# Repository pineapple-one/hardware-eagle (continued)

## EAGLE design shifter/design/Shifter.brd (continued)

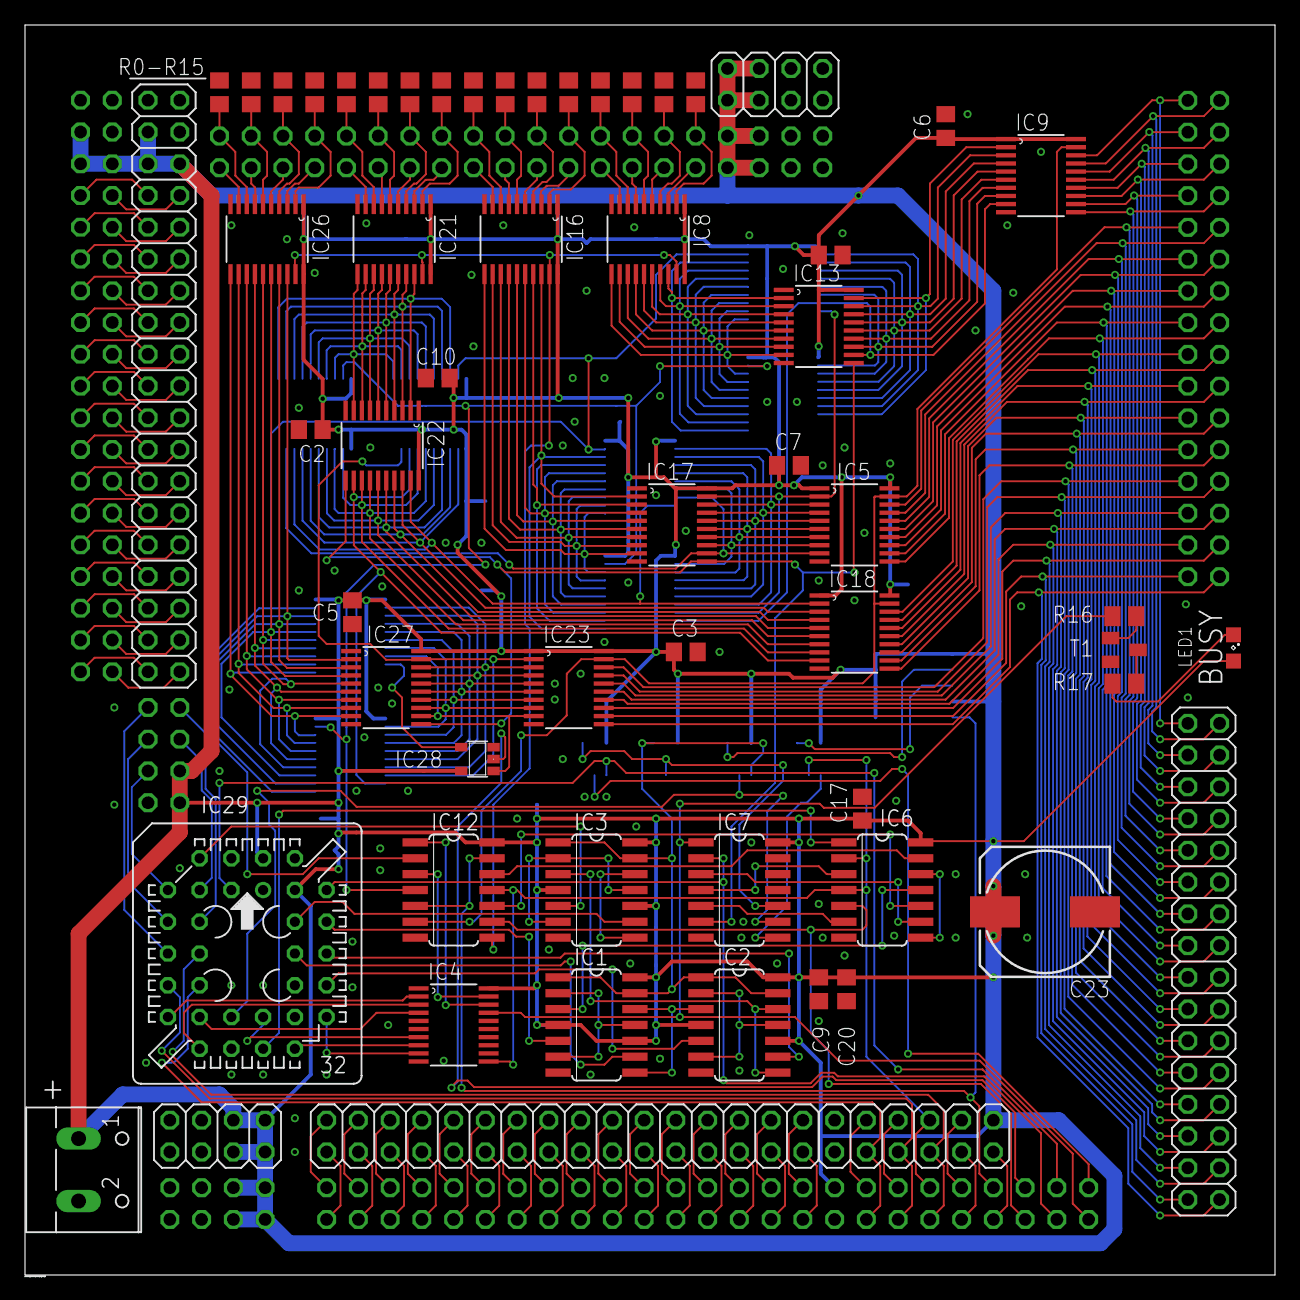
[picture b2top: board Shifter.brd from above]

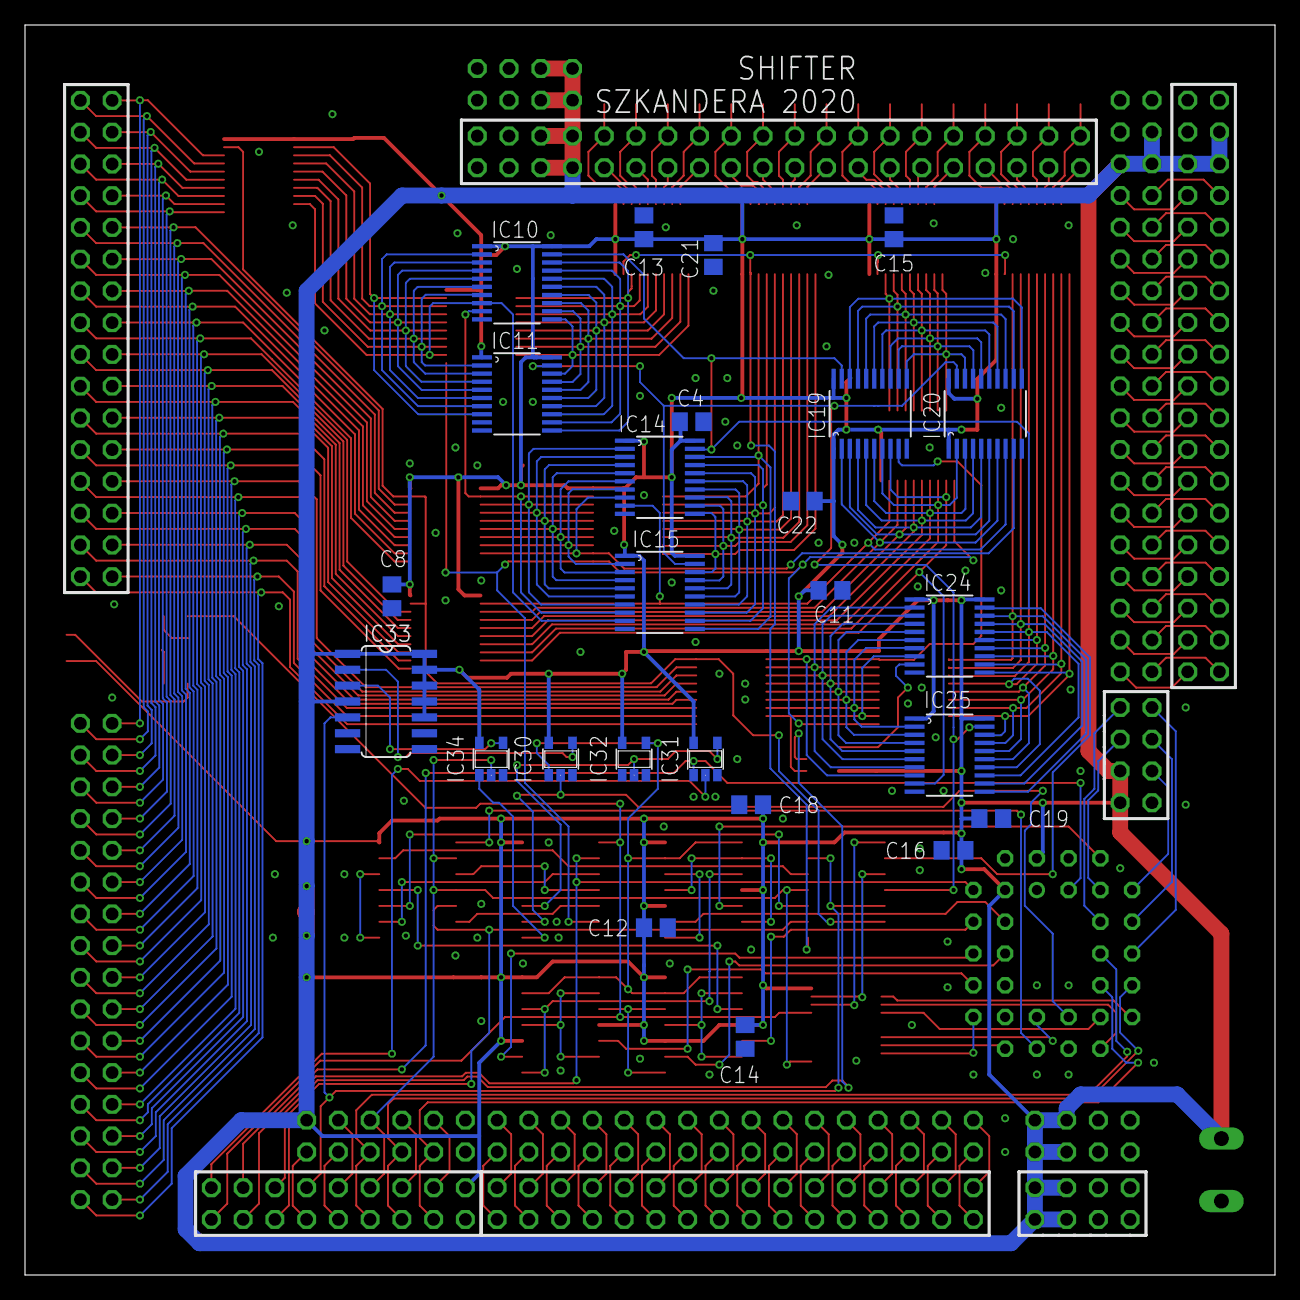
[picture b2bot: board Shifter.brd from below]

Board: 2 copper layers, 100.0 x 100.0 mm, 91 parts (25 on the bottom side), 258 nets.

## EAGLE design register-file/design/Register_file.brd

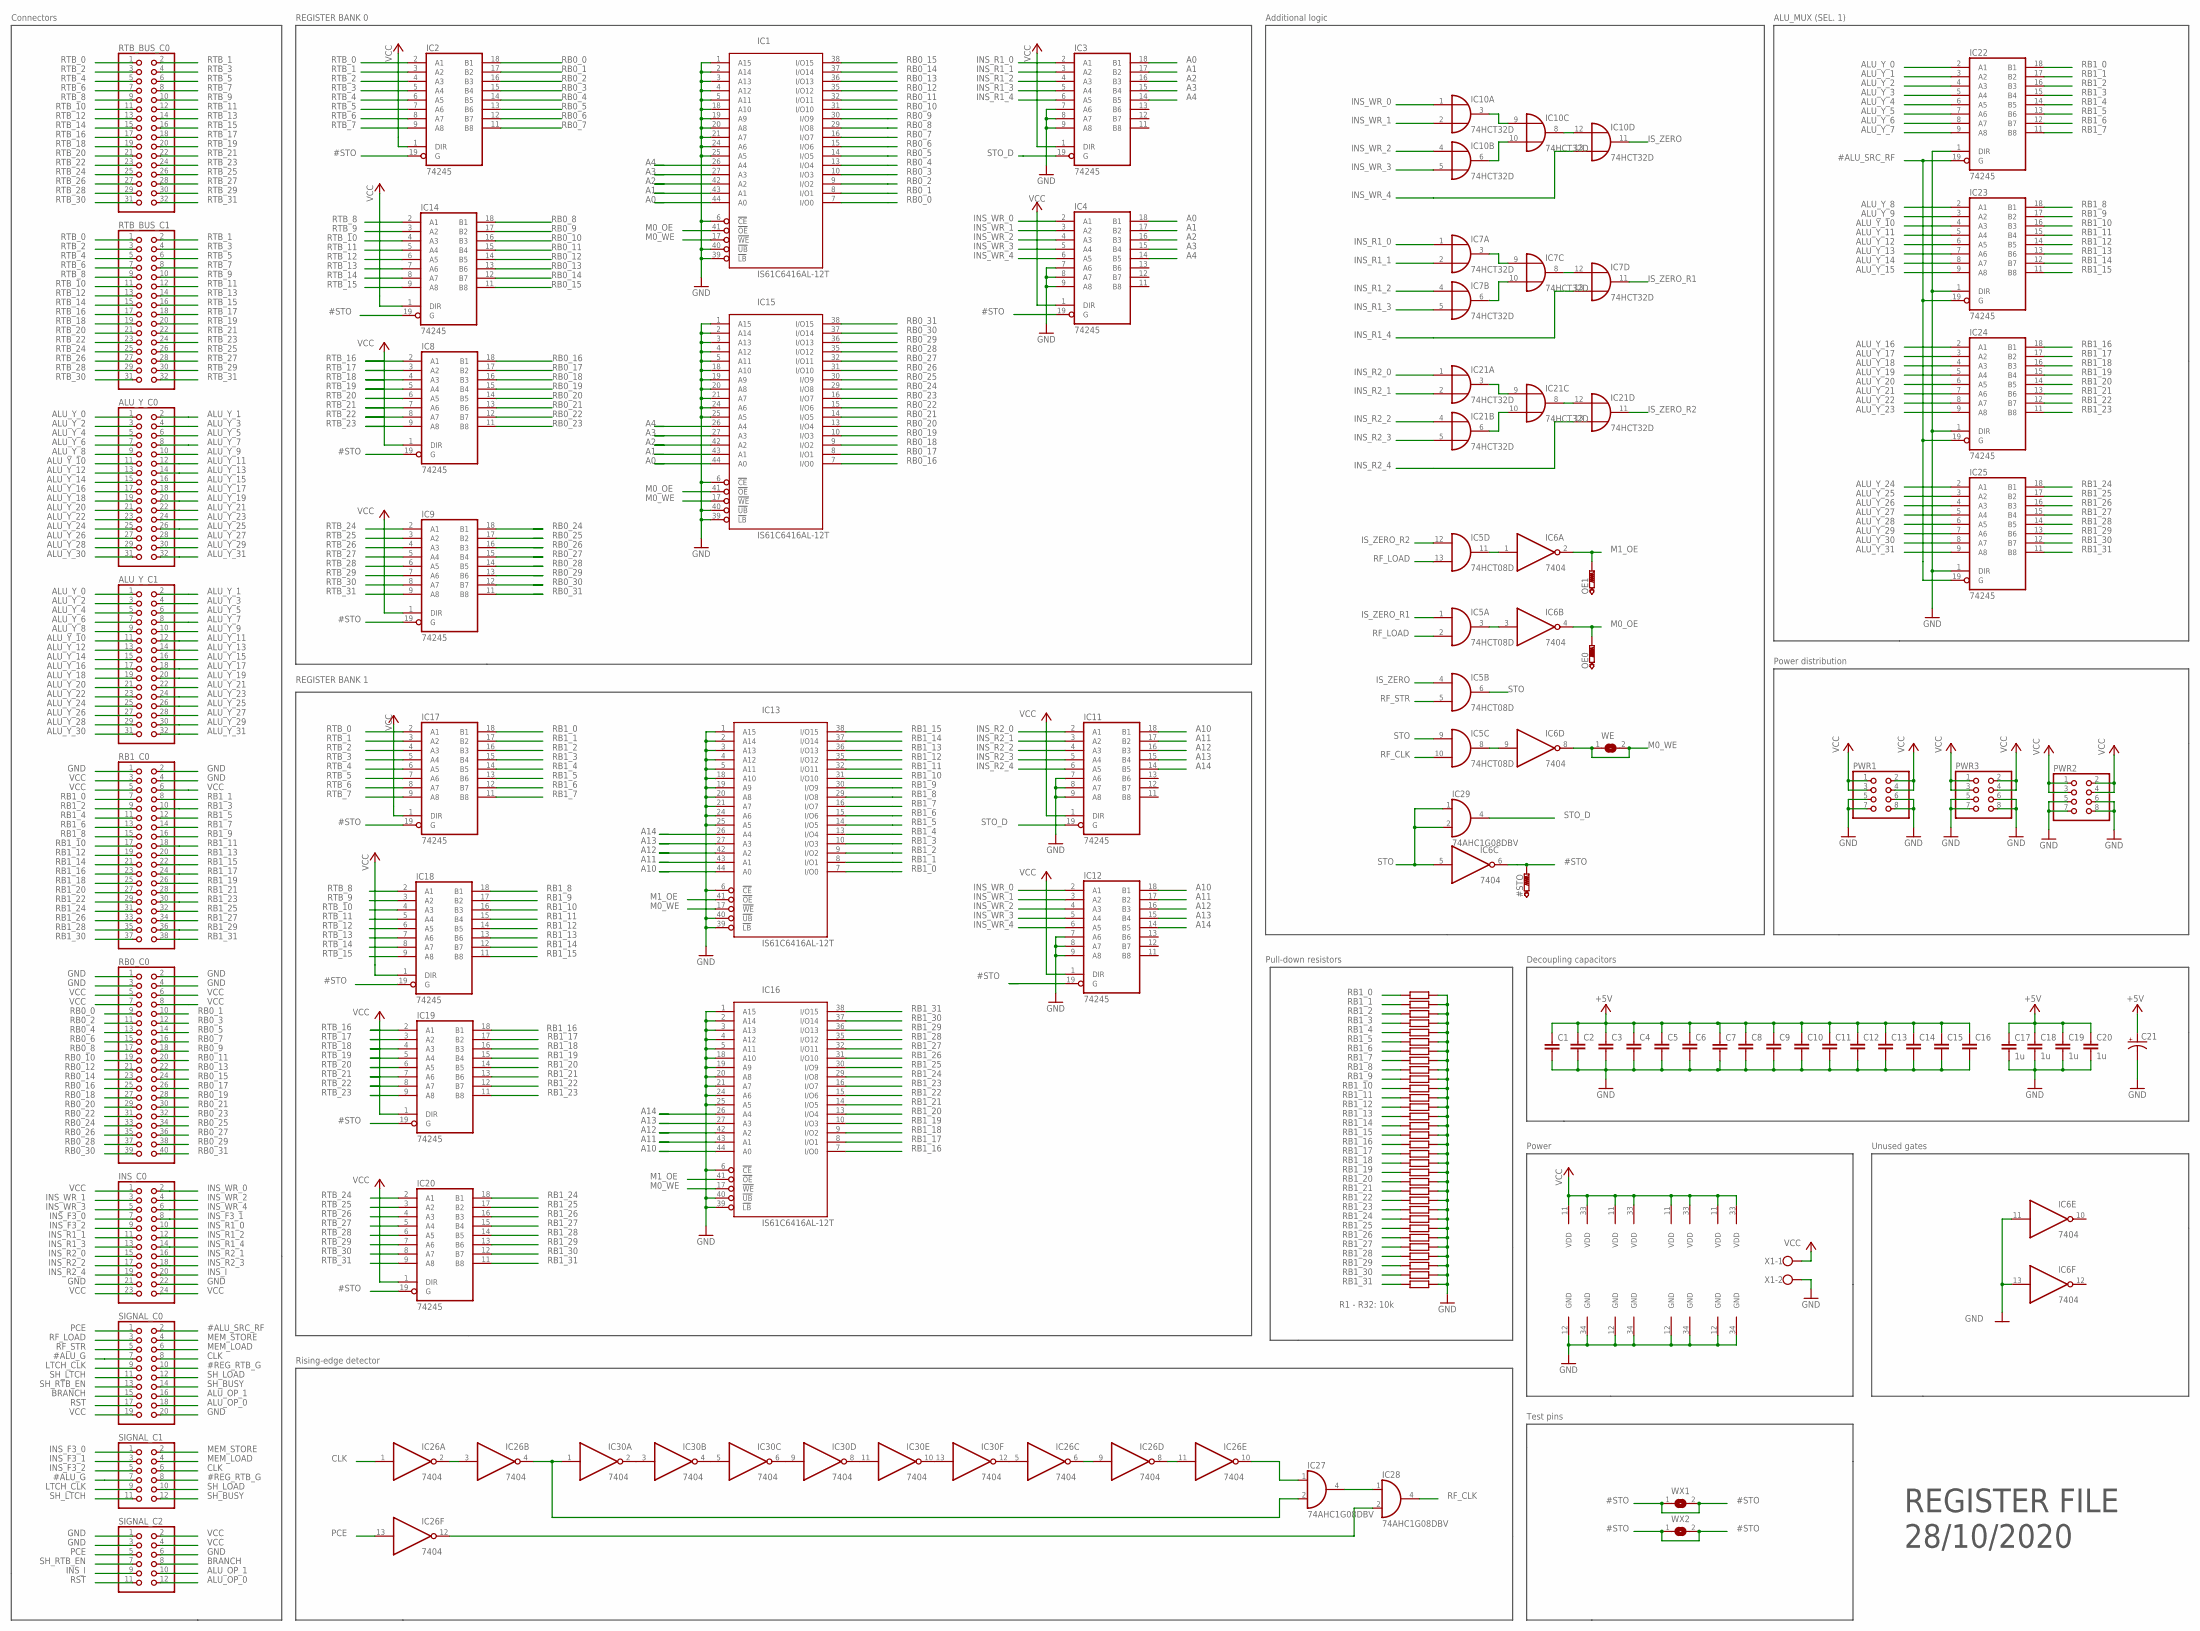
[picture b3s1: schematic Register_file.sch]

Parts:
#STO: PTR1B2,54; B2,54
ALU_Y_C0, ALU_Y_C1: PINHD-2X16; 2X16
C1, C2, C3, C4, C5, C6, C7, C8, C9, C10, C11, C12, C13, C14, C15, C16: C-EUC0805; C0805
C17, C18, C19, C20: 1u; C0805
C21: CAPACITOR-P153CLV-1010; 153CLV-1010
IC1, IC13, IC15, IC16: IS61C6416AL-12T; TSOP-II-44
IC2, IC3, IC4, IC8, IC9, IC11, IC12, IC14, IC17, IC18, IC19, IC20, IC22, IC23, IC24, IC25: 74245; TSSOP20
IC5: 74HCT08D; SO14
IC6, IC26, IC30: 7404; TSSOP14
IC7, IC10, IC21: 74HCT32D; SO14
IC27, IC28, IC29: 74AHC1G08DBV; SOT23-5
INS_C0: PINHD-2X12; 2X12
OE0, OE1: PTR1B2,54; B2,54
PWR1, PWR2, PWR3: PINHD-2X4; 2X04
R33, R34, R35, R36, R37, R38, R39, R40, R41, R42, R43, R44, R45, R46, R47, R48, R49, R50, R51, R52, R53, R54, R55, R56, R57, R58, R59, R60, R61, R62, R63, R64: R-EU_R0805; R0805
RB0_C0: PINHD-2X20; 2X20
RB1_C0: PINHD-2X19; 2X19
RTB_BUS_C0, RTB_BUS_C1: PINHD-2X16; 2X16
SIGNAL_C0: PINHD-2X10; 2X10
SIGNAL_C1, SIGNAL_C2: PINHD-2X6; 2X06
WE: SJ
WX1, WX2: SJ
X1: W237-102

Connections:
#ALU_G: SIGNAL_C0.7, SIGNAL_C1.7
#ALU_SRC_RF: IC22.19 (G), IC23.19 (G), IC24.19 (G), IC25.19 (G), SIGNAL_C0.2
#REG_RTB_G: SIGNAL_C0.10, SIGNAL_C1.8
#STO: #STO.TP, IC2.19 (G), IC4.19 (G), IC6.6 (O), IC8.19 (G), IC9.19 (G), IC12.19 (G), IC14.19 (G), IC17.19 (G), IC18.19 (G), IC19.19 (G), IC20.19 (G), WX1.1, WX1.2, WX2.1, WX2.2
A0: IC1.44 (A0), IC3.18 (B1), IC4.18 (B1), IC15.44 (A0)
A1: IC1.43 (A1), IC3.17 (B2), IC4.17 (B2), IC15.43 (A1)
A2: IC1.42 (A2), IC3.16 (B3), IC4.16 (B3), IC15.42 (A2)
A3: IC1.27 (A3), IC3.15 (B4), IC4.15 (B4), IC15.27 (A3)
A4: IC1.26 (A4), IC3.14 (B5), IC4.14 (B5), IC15.26 (A4)
A10: IC11.18 (B1), IC12.18 (B1), IC13.44 (A0), IC16.44 (A0)
A11: IC11.17 (B2), IC12.17 (B2), IC13.43 (A1), IC16.43 (A1)
A12: IC11.16 (B3), IC12.16 (B3), IC13.42 (A2), IC16.42 (A2)
A13: IC11.15 (B4), IC12.15 (B4), IC13.27 (A3), IC16.27 (A3)
A14: IC11.14 (B5), IC12.14 (B5), IC13.26 (A4), IC16.26 (A4)
ALU_OP_0: SIGNAL_C0.18, SIGNAL_C2.12
ALU_OP_1: SIGNAL_C0.16, SIGNAL_C2.10
ALU_Y_0: ALU_Y_C0.1, ALU_Y_C1.1, IC22.2 (A1)
ALU_Y_1: ALU_Y_C0.2, ALU_Y_C1.2, IC22.3 (A2)
ALU_Y_2: ALU_Y_C0.3, ALU_Y_C1.3, IC22.4 (A3)
ALU_Y_3: ALU_Y_C0.4, ALU_Y_C1.4, IC22.5 (A4)
ALU_Y_4: ALU_Y_C0.5, ALU_Y_C1.5, IC22.6 (A5)
ALU_Y_5: ALU_Y_C0.6, ALU_Y_C1.6, IC22.7 (A6)
ALU_Y_6: ALU_Y_C0.7, ALU_Y_C1.7, IC22.8 (A7)
ALU_Y_7: ALU_Y_C0.8, ALU_Y_C1.8, IC22.9 (A8)
ALU_Y_8: ALU_Y_C0.9, ALU_Y_C1.9, IC23.2 (A1)
ALU_Y_9: ALU_Y_C0.10, ALU_Y_C1.10, IC23.3 (A2)
ALU_Y_10: ALU_Y_C0.11, ALU_Y_C1.11, IC23.4 (A3)
ALU_Y_11: ALU_Y_C0.12, ALU_Y_C1.12, IC23.5 (A4)
ALU_Y_12: ALU_Y_C0.13, ALU_Y_C1.13, IC23.6 (A5)
ALU_Y_13: ALU_Y_C0.14, ALU_Y_C1.14, IC23.7 (A6)
ALU_Y_14: ALU_Y_C0.15, ALU_Y_C1.15, IC23.8 (A7)
ALU_Y_15: ALU_Y_C0.16, ALU_Y_C1.16, IC23.9 (A8)
ALU_Y_16: ALU_Y_C0.17, ALU_Y_C1.17, IC24.2 (A1)
ALU_Y_17: ALU_Y_C0.18, ALU_Y_C1.18, IC24.3 (A2)
ALU_Y_18: ALU_Y_C0.19, ALU_Y_C1.19, IC24.4 (A3)
ALU_Y_19: ALU_Y_C0.20, ALU_Y_C1.20, IC24.5 (A4)
ALU_Y_20: ALU_Y_C0.21, ALU_Y_C1.21, IC24.6 (A5)
ALU_Y_21: ALU_Y_C0.22, ALU_Y_C1.22, IC24.7 (A6)
ALU_Y_22: ALU_Y_C0.23, ALU_Y_C1.23, IC24.8 (A7)
ALU_Y_23: ALU_Y_C0.24, ALU_Y_C1.24, IC24.9 (A8)
ALU_Y_24: ALU_Y_C0.25, ALU_Y_C1.25, IC25.2 (A1)
ALU_Y_25: ALU_Y_C0.26, ALU_Y_C1.26, IC25.3 (A2)
ALU_Y_26: ALU_Y_C0.27, ALU_Y_C1.27, IC25.4 (A3)
ALU_Y_27: ALU_Y_C0.28, ALU_Y_C1.28, IC25.5 (A4)
ALU_Y_28: ALU_Y_C0.29, ALU_Y_C1.29, IC25.6 (A5)
ALU_Y_29: ALU_Y_C0.30, ALU_Y_C1.30, IC25.7 (A6)
ALU_Y_30: ALU_Y_C0.31, ALU_Y_C1.31, IC25.8 (A7)
ALU_Y_31: ALU_Y_C0.32, ALU_Y_C1.32, IC25.9 (A8)
BRANCH: SIGNAL_C0.15, SIGNAL_C2.8
CLK: IC26.1 (I), SIGNAL_C0.8, SIGNAL_C1.6
GND: C1.2, C2.2, C3.2, C4.2, C5.2, C6.2, C7.2, C8.2, C9.2, C10.2, C11.2, C12.2, C13.2, C14.2, C15.2, C16.2, C17.2, C18.2, C19.2, C20.2, C21.-, IC1.1 (A15), IC1.2 (A14), IC1.3 (A13), IC1.4 (A12), IC1.5 (A11), IC1.6 (!CE), IC1.12 (GND), IC1.18 (A10), IC1.19 (A9), IC1.20 (A8), IC1.21 (A7), IC1.24 (A6), IC1.25 (A5), IC1.34 (GND), IC1.39 (!LB), IC1.40 (!UB), IC2.10 (GND), IC3.7 (A6), IC3.8 (A7), IC3.9 (A8), IC3.10 (GND), IC4.7 (A6), IC4.8 (A7), IC4.9 (A8), IC4.10 (GND), IC5.7 (GND), IC6.7 (GND), IC6.11 (I), IC6.13 (I), IC7.7 (GND), IC8.10 (GND), IC9.10 (GND), IC10.7 (GND), IC11.7 (A6), IC11.8 (A7), IC11.9 (A8), IC11.10 (GND), IC12.7 (A6), IC12.8 (A7), IC12.9 (A8), IC12.10 (GND), IC13.1 (A15), IC13.2 (A14), IC13.3 (A13), IC13.4 (A12), IC13.5 (A11), IC13.6 (!CE), IC13.12 (GND), IC13.18 (A10), IC13.19 (A9), IC13.20 (A8), IC13.21 (A7), IC13.24 (A6), IC13.25 (A5), IC13.34 (GND), IC13.39 (!LB), IC13.40 (!UB), IC14.10 (GND), IC15.1 (A15), IC15.2 (A14), IC15.3 (A13), IC15.4 (A12), IC15.5 (A11), IC15.6 (!CE), IC15.12 (GND), IC15.18 (A10), IC15.19 (A9), IC15.20 (A8), IC15.21 (A7), IC15.24 (A6), IC15.25 (A5), IC15.34 (GND), IC15.39 (!LB), IC15.40 (!UB), IC16.1 (A15), IC16.2 (A14), IC16.3 (A13), IC16.4 (A12), IC16.5 (A11), IC16.6 (!CE), IC16.12 (GND), IC16.18 (A10), IC16.19 (A9), IC16.20 (A8), IC16.21 (A7), IC16.24 (A6), IC16.25 (A5), IC16.34 (GND), IC16.39 (!LB), IC16.40 (!UB), IC17.10 (GND), IC18.10 (GND), IC19.10 (GND), IC20.10 (GND), IC21.7 (GND), IC22.1 (DIR), IC22.10 (GND), IC23.1 (DIR), IC23.10 (GND), IC24.1 (DIR), IC24.10 (GND), IC25.1 (DIR), IC25.10 (GND), IC26.7 (GND), IC27.3 (GND), IC28.3 (GND), IC29.3 (GND), IC30.7 (GND), INS_C0.21, INS_C0.22, PWR1.5, PWR1.6, PWR1.7, PWR1.8, PWR2.5, PWR2.6, PWR2.7, PWR2.8, PWR3.5, PWR3.6, PWR3.7, PWR3.8, R33.2, R34.2, R35.2, R36.2, R37.2, R38.2, R39.2, R40.2, R41.2, R42.2, R43.2, R44.2, R45.2, R46.2, R47.2, R48.2, R49.2, R50.2, R51.2, R52.2, R53.2, R54.2, R55.2, R56.2, R57.2, R58.2, R59.2, R60.2, R61.2, R62.2, R63.2, R64.2, RB0_C0.1, RB0_C0.2, RB0_C0.3, RB0_C0.4, RB1_C0.1, RB1_C0.2, RB1_C0.4, SIGNAL_C0.20, SIGNAL_C2.1, SIGNAL_C2.3, SIGNAL_C2.6, X1.2
INS_F3_0: INS_C0.7, SIGNAL_C1.1
INS_F3_1: INS_C0.8, SIGNAL_C1.3
INS_F3_2: INS_C0.9, SIGNAL_C1.5
INS_I: INS_C0.20, SIGNAL_C2.9
INS_R1_0: IC3.2 (A1), IC7.1 (I0), INS_C0.10
INS_R1_1: IC3.3 (A2), IC7.2 (I1), INS_C0.11
INS_R1_2: IC3.4 (A3), IC7.4 (I0), INS_C0.12
INS_R1_3: IC3.5 (A4), IC7.5 (I1), INS_C0.13
INS_R1_4: IC3.6 (A5), IC7.13 (I1), INS_C0.14
INS_R2_0: IC11.2 (A1), IC21.1 (I0), INS_C0.15
INS_R2_1: IC11.3 (A2), IC21.2 (I1), INS_C0.16
INS_R2_2: IC11.4 (A3), IC21.4 (I0), INS_C0.17
INS_R2_3: IC11.5 (A4), IC21.5 (I1), INS_C0.18
INS_R2_4: IC11.6 (A5), IC21.13 (I1), INS_C0.19
INS_WR_0: IC4.2 (A1), IC10.1 (I0), IC12.2 (A1), INS_C0.2
INS_WR_1: IC4.3 (A2), IC10.2 (I1), IC12.3 (A2), INS_C0.3
INS_WR_2: IC4.4 (A3), IC10.4 (I0), IC12.4 (A3), INS_C0.4
INS_WR_3: IC4.5 (A4), IC10.5 (I1), IC12.5 (A4), INS_C0.5
INS_WR_4: IC4.6 (A5), IC10.13 (I1), IC12.6 (A5), INS_C0.6
IS_ZERO: IC5.4 (I0), IC10.11 (O)
IS_ZERO_R1: IC5.1 (I0), IC7.11 (O)
IS_ZERO_R2: IC5.12 (I0), IC21.11 (O)
LTCH_CLK: SIGNAL_C0.9, SIGNAL_C1.9
M0_OE: IC1.41 (!OE), IC6.4 (O), IC15.41 (!OE), OE0.TP
M0_WE: IC1.17 (!WE), IC6.8 (O), IC13.17 (!WE), IC15.17 (!WE), IC16.17 (!WE), WE.1, WE.2
M1_OE: IC6.2 (O), IC13.41 (!OE), IC16.41 (!OE), OE1.TP
MEM_LOAD: SIGNAL_C0.6, SIGNAL_C1.4
MEM_STORE: SIGNAL_C0.4, SIGNAL_C1.2
unnamed: IC7.3 (O), IC7.9 (I0)
unnamed: IC7.6 (O), IC7.10 (I1)
unnamed: IC10.3 (O), IC10.9 (I0)
unnamed: IC10.6 (O), IC10.10 (I1)
unnamed: IC10.8 (O), IC10.12 (I0)
unnamed: IC7.8 (O), IC7.12 (I0)
unnamed: IC5.3 (O), IC6.3 (I)
unnamed: IC5.8 (O), IC6.9 (I)
unnamed: IC21.3 (O), IC21.9 (I0)
unnamed: IC21.6 (O), IC21.10 (I1)
unnamed: IC21.8 (O), IC21.12 (I0)
unnamed: IC5.11 (O), IC6.1 (I)
unnamed: IC30.2 (O), IC30.3 (I)
unnamed: IC30.4 (O), IC30.5 (I)
unnamed: IC30.6 (O), IC30.9 (I)
unnamed: IC26.2 (O), IC26.3 (I)
unnamed: IC26.4 (O), IC27.2 (I1), IC30.1 (I)
unnamed: IC26.6 (O), IC26.9 (I)
unnamed: IC26.8 (O), IC26.11 (I)
unnamed: IC26.10 (O), IC27.1 (I0)
unnamed: IC27.4 (O), IC28.1 (I0)
unnamed: IC26.12 (O), IC28.2 (I1)
unnamed: IC30.8 (O), IC30.11 (I)
unnamed: IC30.10 (O), IC30.13 (I)
unnamed: IC26.5 (I), IC30.12 (O)
PCE: IC26.13 (I), SIGNAL_C0.1, SIGNAL_C2.5
RB0_0: IC1.7 (I/O0), IC2.18 (B1), RB0_C0.9
RB0_1: IC1.8 (I/O1), IC2.17 (B2), RB0_C0.10
RB0_2: IC1.9 (I/O2), IC2.16 (B3), RB0_C0.11
RB0_3: IC1.10 (I/O3), IC2.15 (B4), RB0_C0.12
RB0_4: IC1.13 (I/O4), IC2.14 (B5), RB0_C0.13
RB0_5: IC1.14 (I/O5), IC2.13 (B6), RB0_C0.14
RB0_6: IC1.15 (I/O6), IC2.12 (B7), RB0_C0.15
RB0_7: IC1.16 (I/O7), IC2.11 (B8), RB0_C0.16
RB0_8: IC1.29 (I/O8), IC14.18 (B1), RB0_C0.17
RB0_9: IC1.30 (I/O9), IC14.17 (B2), RB0_C0.18
RB0_10: IC1.31 (I/O10), IC14.16 (B3), RB0_C0.19
RB0_11: IC1.32 (I/O11), IC14.15 (B4), RB0_C0.20
RB0_12: IC1.35 (I/O12), IC14.14 (B5), RB0_C0.21
RB0_13: IC1.36 (I/O13), IC14.13 (B6), RB0_C0.22
RB0_14: IC1.37 (I/O14), IC14.12 (B7), RB0_C0.23
RB0_15: IC1.38 (I/O15), IC14.11 (B8), RB0_C0.24
RB0_16: IC8.18 (B1), IC15.7 (I/O0), RB0_C0.25
RB0_17: IC8.17 (B2), IC15.8 (I/O1), RB0_C0.26
RB0_18: IC8.16 (B3), IC15.9 (I/O2), RB0_C0.27
RB0_19: IC8.15 (B4), IC15.10 (I/O3), RB0_C0.28
RB0_20: IC8.14 (B5), IC15.13 (I/O4), RB0_C0.29
RB0_21: IC8.13 (B6), IC15.14 (I/O5), RB0_C0.30
RB0_22: IC8.12 (B7), IC15.15 (I/O6), RB0_C0.31
RB0_23: IC8.11 (B8), IC15.16 (I/O7), RB0_C0.32
RB0_24: IC9.18 (B1), IC15.29 (I/O8), RB0_C0.33
RB0_25: IC9.17 (B2), IC15.30 (I/O9), RB0_C0.34
RB0_26: IC9.16 (B3), IC15.31 (I/O10), RB0_C0.35
RB0_27: IC9.15 (B4), IC15.32 (I/O11), RB0_C0.36
RB0_28: IC9.14 (B5), IC15.35 (I/O12), RB0_C0.37
RB0_29: IC9.13 (B6), IC15.36 (I/O13), RB0_C0.38
RB0_30: IC9.12 (B7), IC15.37 (I/O14), RB0_C0.39
RB0_31: IC9.11 (B8), IC15.38 (I/O15), RB0_C0.40
RB1_0: IC13.7 (I/O0), IC17.18 (B1), IC22.18 (B1), R33.1, RB1_C0.7
RB1_1: IC13.8 (I/O1), IC17.17 (B2), IC22.17 (B2), R34.1, RB1_C0.8
RB1_2: IC13.9 (I/O2), IC17.16 (B3), IC22.16 (B3), R35.1, RB1_C0.9
RB1_3: IC13.10 (I/O3), IC17.15 (B4), IC22.15 (B4), R36.1, RB1_C0.10
RB1_4: IC13.13 (I/O4), IC17.14 (B5), IC22.14 (B5), R37.1, RB1_C0.11
RB1_5: IC13.14 (I/O5), IC17.13 (B6), IC22.13 (B6), R38.1, RB1_C0.12
RB1_6: IC13.15 (I/O6), IC17.12 (B7), IC22.12 (B7), R39.1, RB1_C0.13
RB1_7: IC13.16 (I/O7), IC17.11 (B8), IC22.11 (B8), R40.1, RB1_C0.14
RB1_8: IC13.29 (I/O8), IC18.18 (B1), IC23.18 (B1), R41.1, RB1_C0.15
RB1_9: IC13.30 (I/O9), IC18.17 (B2), IC23.17 (B2), R42.1, RB1_C0.16
RB1_10: IC13.31 (I/O10), IC18.16 (B3), IC23.16 (B3), R43.1, RB1_C0.17
RB1_11: IC13.32 (I/O11), IC18.15 (B4), IC23.15 (B4), R44.1, RB1_C0.18
RB1_12: IC13.35 (I/O12), IC18.14 (B5), IC23.14 (B5), R45.1, RB1_C0.19
RB1_13: IC13.36 (I/O13), IC18.13 (B6), IC23.13 (B6), R46.1, RB1_C0.20
RB1_14: IC13.37 (I/O14), IC18.12 (B7), IC23.12 (B7), R47.1, RB1_C0.21
RB1_15: IC13.38 (I/O15), IC18.11 (B8), IC23.11 (B8), R48.1, RB1_C0.22
RB1_16: IC16.7 (I/O0), IC19.18 (B1), IC24.18 (B1), R49.1, RB1_C0.23
RB1_17: IC16.8 (I/O1), IC19.17 (B2), IC24.17 (B2), R50.1, RB1_C0.24
RB1_18: IC16.9 (I/O2), IC19.16 (B3), IC24.16 (B3), R51.1, RB1_C0.25
RB1_19: IC16.10 (I/O3), IC19.15 (B4), IC24.15 (B4), R52.1, RB1_C0.26
RB1_20: IC16.13 (I/O4), IC19.14 (B5), IC24.14 (B5), R53.1, RB1_C0.27
RB1_21: IC16.14 (I/O5), IC19.13 (B6), IC24.13 (B6), R54.1, RB1_C0.28
RB1_22: IC16.15 (I/O6), IC19.12 (B7), IC24.12 (B7), R55.1, RB1_C0.29
RB1_23: IC16.16 (I/O7), IC19.11 (B8), IC24.11 (B8), R56.1, RB1_C0.30
RB1_24: IC16.29 (I/O8), IC20.18 (B1), IC25.18 (B1), R57.1, RB1_C0.31
RB1_25: IC16.30 (I/O9), IC20.17 (B2), IC25.17 (B2), R58.1, RB1_C0.32
RB1_26: IC16.31 (I/O10), IC20.16 (B3), IC25.16 (B3), R59.1, RB1_C0.33
RB1_27: IC16.32 (I/O11), IC20.15 (B4), IC25.15 (B4), R60.1, RB1_C0.34
RB1_28: IC16.35 (I/O12), IC20.14 (B5), IC25.14 (B5), R61.1, RB1_C0.35
RB1_29: IC16.36 (I/O13), IC20.13 (B6), IC25.13 (B6), R62.1, RB1_C0.36
RB1_30: IC16.37 (I/O14), IC20.12 (B7), IC25.12 (B7), R63.1, RB1_C0.37
RB1_31: IC16.38 (I/O15), IC20.11 (B8), IC25.11 (B8), R64.1, RB1_C0.38
RF_CLK: IC5.10 (I1), IC28.4 (O)
RF_LOAD: IC5.2 (I1), IC5.13 (I1), SIGNAL_C0.3
RF_STR: IC5.5 (I1), SIGNAL_C0.5
RST: SIGNAL_C0.17, SIGNAL_C2.11
RTB_0: IC2.2 (A1), IC17.2 (A1), RTB_BUS_C0.1, RTB_BUS_C1.1
RTB_1: IC2.3 (A2), IC17.3 (A2), RTB_BUS_C0.2, RTB_BUS_C1.2
RTB_2: IC2.4 (A3), IC17.4 (A3), RTB_BUS_C0.3, RTB_BUS_C1.3
RTB_3: IC2.5 (A4), IC17.5 (A4), RTB_BUS_C0.4, RTB_BUS_C1.4
RTB_4: IC2.6 (A5), IC17.6 (A5), RTB_BUS_C0.5, RTB_BUS_C1.5
RTB_5: IC2.7 (A6), IC17.7 (A6), RTB_BUS_C0.6, RTB_BUS_C1.6
RTB_6: IC2.8 (A7), IC17.8 (A7), RTB_BUS_C0.7, RTB_BUS_C1.7
RTB_7: IC2.9 (A8), IC17.9 (A8), RTB_BUS_C0.8, RTB_BUS_C1.8
RTB_8: IC14.2 (A1), IC18.2 (A1), RTB_BUS_C0.9, RTB_BUS_C1.9
RTB_9: IC14.3 (A2), IC18.3 (A2), RTB_BUS_C0.10, RTB_BUS_C1.10
RTB_10: IC14.4 (A3), IC18.4 (A3), RTB_BUS_C0.11, RTB_BUS_C1.11
RTB_11: IC14.5 (A4), IC18.5 (A4), RTB_BUS_C0.12, RTB_BUS_C1.12
RTB_12: IC14.6 (A5), IC18.6 (A5), RTB_BUS_C0.13, RTB_BUS_C1.13
RTB_13: IC14.7 (A6), IC18.7 (A6), RTB_BUS_C0.14, RTB_BUS_C1.14
RTB_14: IC14.8 (A7), IC18.8 (A7), RTB_BUS_C0.15, RTB_BUS_C1.15
RTB_15: IC14.9 (A8), IC18.9 (A8), RTB_BUS_C0.16, RTB_BUS_C1.16
RTB_16: IC8.2 (A1), IC19.2 (A1), RTB_BUS_C0.17, RTB_BUS_C1.17
RTB_17: IC8.3 (A2), IC19.3 (A2), RTB_BUS_C0.18, RTB_BUS_C1.18
RTB_18: IC8.4 (A3), IC19.4 (A3), RTB_BUS_C0.19, RTB_BUS_C1.19
RTB_19: IC8.5 (A4), IC19.5 (A4), RTB_BUS_C0.20, RTB_BUS_C1.20
RTB_20: IC8.6 (A5), IC19.6 (A5), RTB_BUS_C0.21, RTB_BUS_C1.21
RTB_21: IC8.7 (A6), IC19.7 (A6), RTB_BUS_C0.22, RTB_BUS_C1.22
RTB_22: IC8.8 (A7), IC19.8 (A7), RTB_BUS_C0.23, RTB_BUS_C1.23
RTB_23: IC8.9 (A8), IC19.9 (A8), RTB_BUS_C0.24, RTB_BUS_C1.24
RTB_24: IC9.2 (A1), IC20.2 (A1), RTB_BUS_C0.25, RTB_BUS_C1.25
RTB_25: IC9.3 (A2), IC20.3 (A2), RTB_BUS_C0.26, RTB_BUS_C1.26
RTB_26: IC9.4 (A3), IC20.4 (A3), RTB_BUS_C0.27, RTB_BUS_C1.27
RTB_27: IC9.5 (A4), IC20.5 (A4), RTB_BUS_C0.28, RTB_BUS_C1.28
RTB_28: IC9.6 (A5), IC20.6 (A5), RTB_BUS_C0.29, RTB_BUS_C1.29
RTB_29: IC9.7 (A6), IC20.7 (A6), RTB_BUS_C0.30, RTB_BUS_C1.30
RTB_30: IC9.8 (A7), IC20.8 (A7), RTB_BUS_C0.31, RTB_BUS_C1.31
RTB_31: IC9.9 (A8), IC20.9 (A8), RTB_BUS_C0.32, RTB_BUS_C1.32
SH_BUSY: SIGNAL_C0.14, SIGNAL_C1.12
SH_LOAD: SIGNAL_C0.12, SIGNAL_C1.10
SH_LTCH: SIGNAL_C0.11, SIGNAL_C1.11
SH_RTB_EN: SIGNAL_C0.13, SIGNAL_C2.7
STO: IC5.6 (O), IC5.9 (I0), IC6.5 (I), IC29.1 (I0), IC29.2 (I1)
STO_D: IC3.19 (G), IC11.19 (G), IC29.4 (O)
VCC: C1.1, C2.1, C3.1, C4.1, C5.1, C6.1, C7.1, C8.1, C9.1, C10.1, C11.1, C12.1, C13.1, C14.1, C15.1, C16.1, C17.1, C18.1, C19.1, C20.1, C21.+, IC1.11 (VDD), IC1.33 (VDD), IC2.1 (DIR), IC2.20 (VCC), IC3.1 (DIR), IC3.20 (VCC), IC4.1 (DIR), IC4.20 (VCC), IC5.14 (VCC), IC6.14 (VCC), IC7.14 (VCC), IC8.1 (DIR), IC8.20 (VCC), IC9.1 (DIR), IC9.20 (VCC), IC10.14 (VCC), IC11.1 (DIR), IC11.20 (VCC), IC12.1 (DIR), IC12.20 (VCC), IC13.11 (VDD), IC13.33 (VDD), IC14.1 (DIR), IC14.20 (VCC), IC15.11 (VDD), IC15.33 (VDD), IC16.11 (VDD), IC16.33 (VDD), IC17.1 (DIR), IC17.20 (VCC), IC18.1 (DIR), IC18.20 (VCC), IC19.1 (DIR), IC19.20 (VCC), IC20.1 (DIR), IC20.20 (VCC), IC21.14 (VCC), IC22.20 (VCC), IC23.20 (VCC), IC24.20 (VCC), IC25.20 (VCC), IC26.14 (VCC), IC27.5 (VCC), IC28.5 (VCC), IC29.5 (VCC), IC30.14 (VCC), INS_C0.1, INS_C0.23, INS_C0.24, PWR1.1, PWR1.2, PWR1.3, PWR1.4, PWR2.1, PWR2.2, PWR2.3, PWR2.4, PWR3.1, PWR3.2, PWR3.3, PWR3.4, RB0_C0.5, RB0_C0.6, RB0_C0.7, RB0_C0.8, RB1_C0.3, RB1_C0.5, RB1_C0.6, SIGNAL_C0.19, SIGNAL_C2.2, SIGNAL_C2.4, X1.1

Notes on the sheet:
R1 - R32: 10k
REGISTER BANK 0
REGISTER FILE 28/10/2020
REGISTER BANK 1
Additional logic
ALU_MUX (SEL. 1)
Connectors
Rising-edge detector
Pull-down resistors
Power distribution
Decoupling capacitors
Power
Unused gates
Test pins

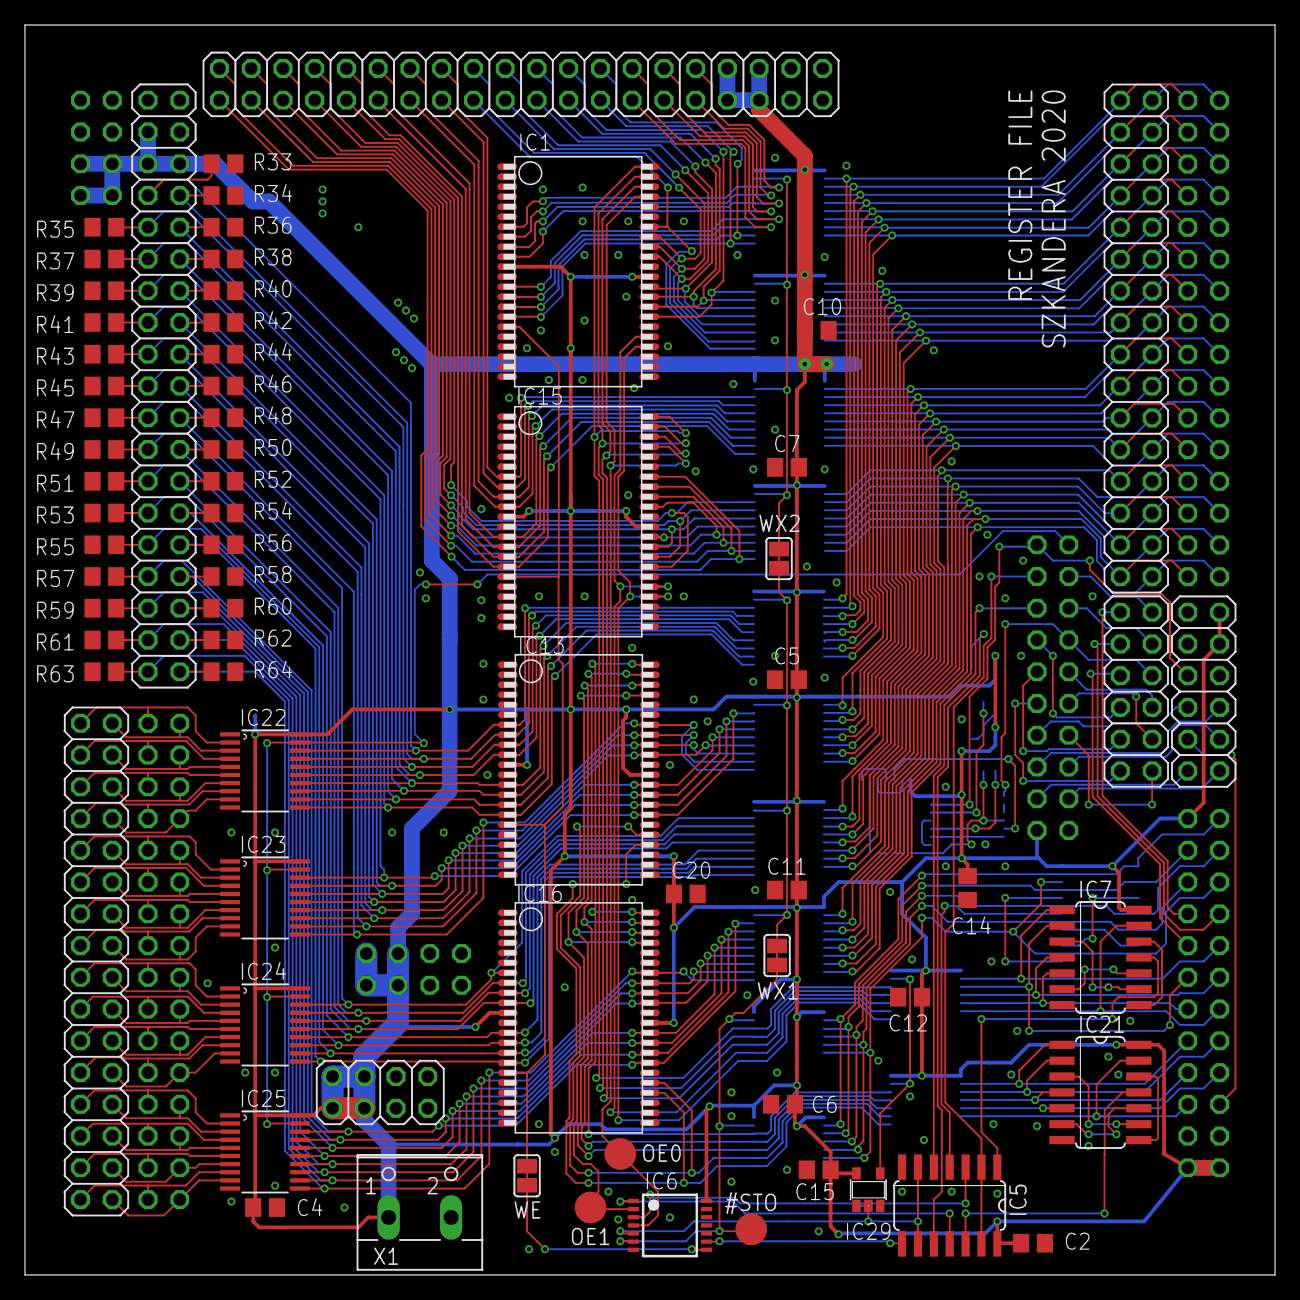
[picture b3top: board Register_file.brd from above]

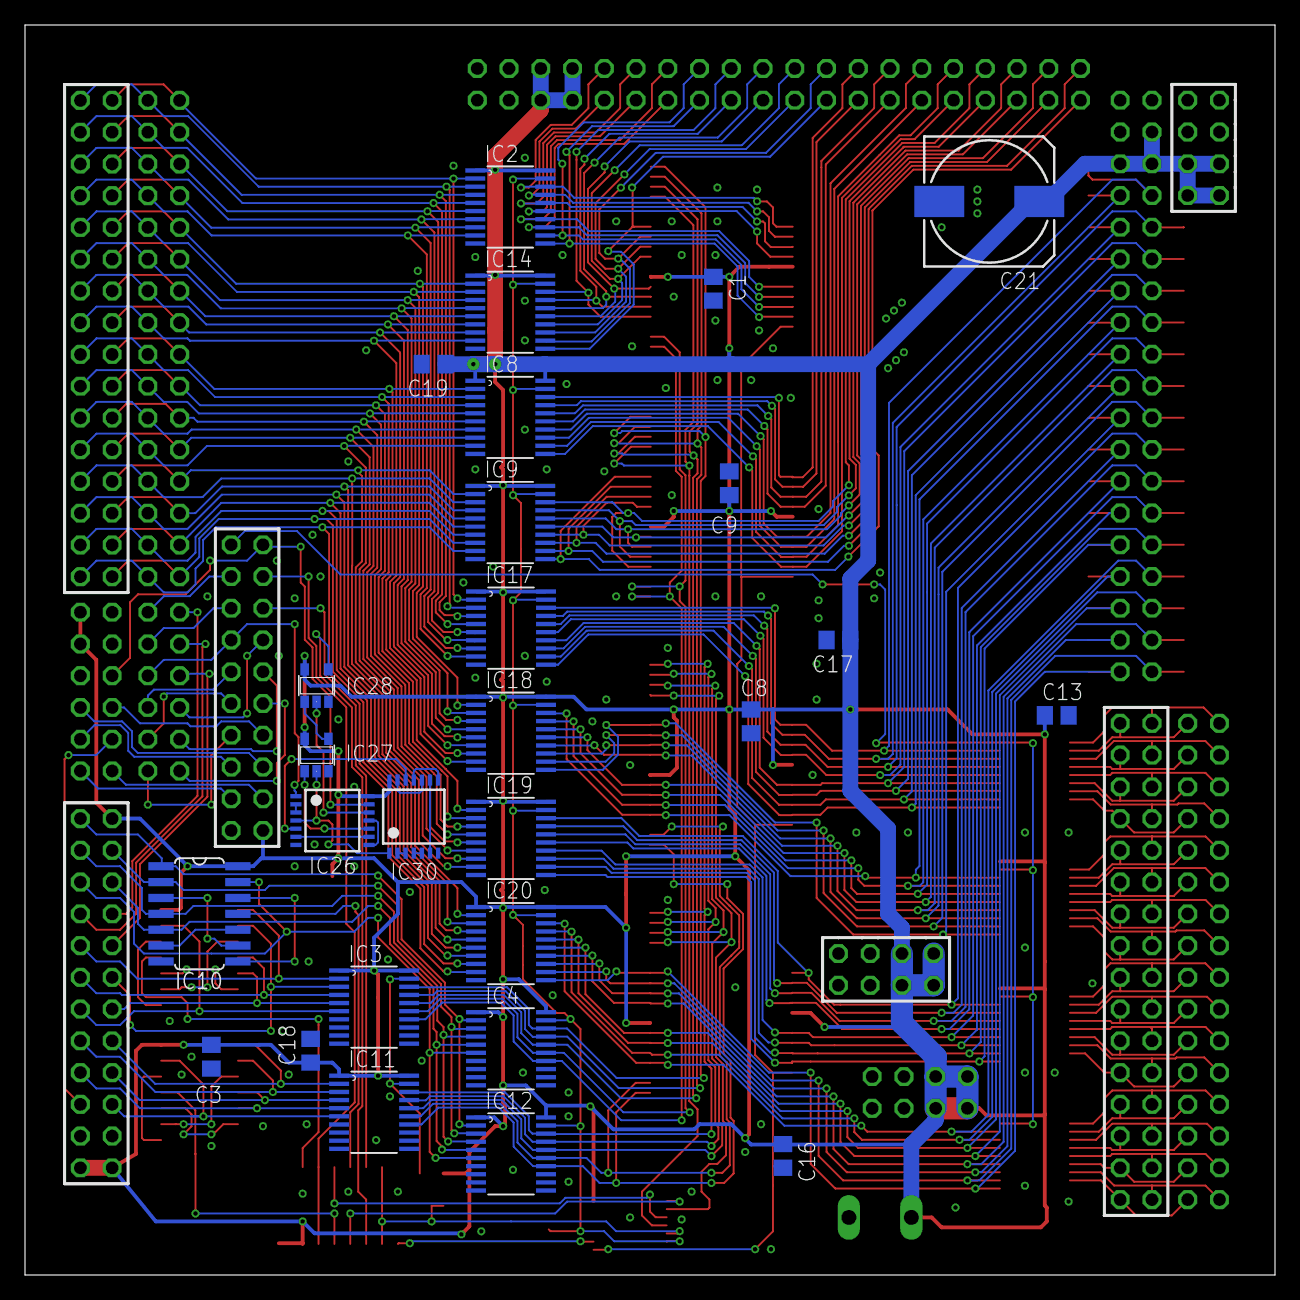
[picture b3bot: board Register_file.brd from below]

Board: 2 copper layers, 100.0 x 100.0 mm, 103 parts (27 on the bottom side), 212 nets.
